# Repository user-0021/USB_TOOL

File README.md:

# BLDC_MOTER_DRIVER_ALPHA
この回路は15~30Vほどの電源で回す三層モータードライバー向けの回路です
設計上の連続最大電流は10Aです(実験してないのでだめかも)
ヒートシンクとかで冷やしながらならFET的には35A行ける
## インターフェース
制御用のインターフェースはLVDSとなっております。
## 機能
ゲートドライバーに過電圧過電流などの保護があります  
ホールセンサの入力はアナログ入力になっているのでプログラムを書けばどのセンサタイプでも  
いけるはず

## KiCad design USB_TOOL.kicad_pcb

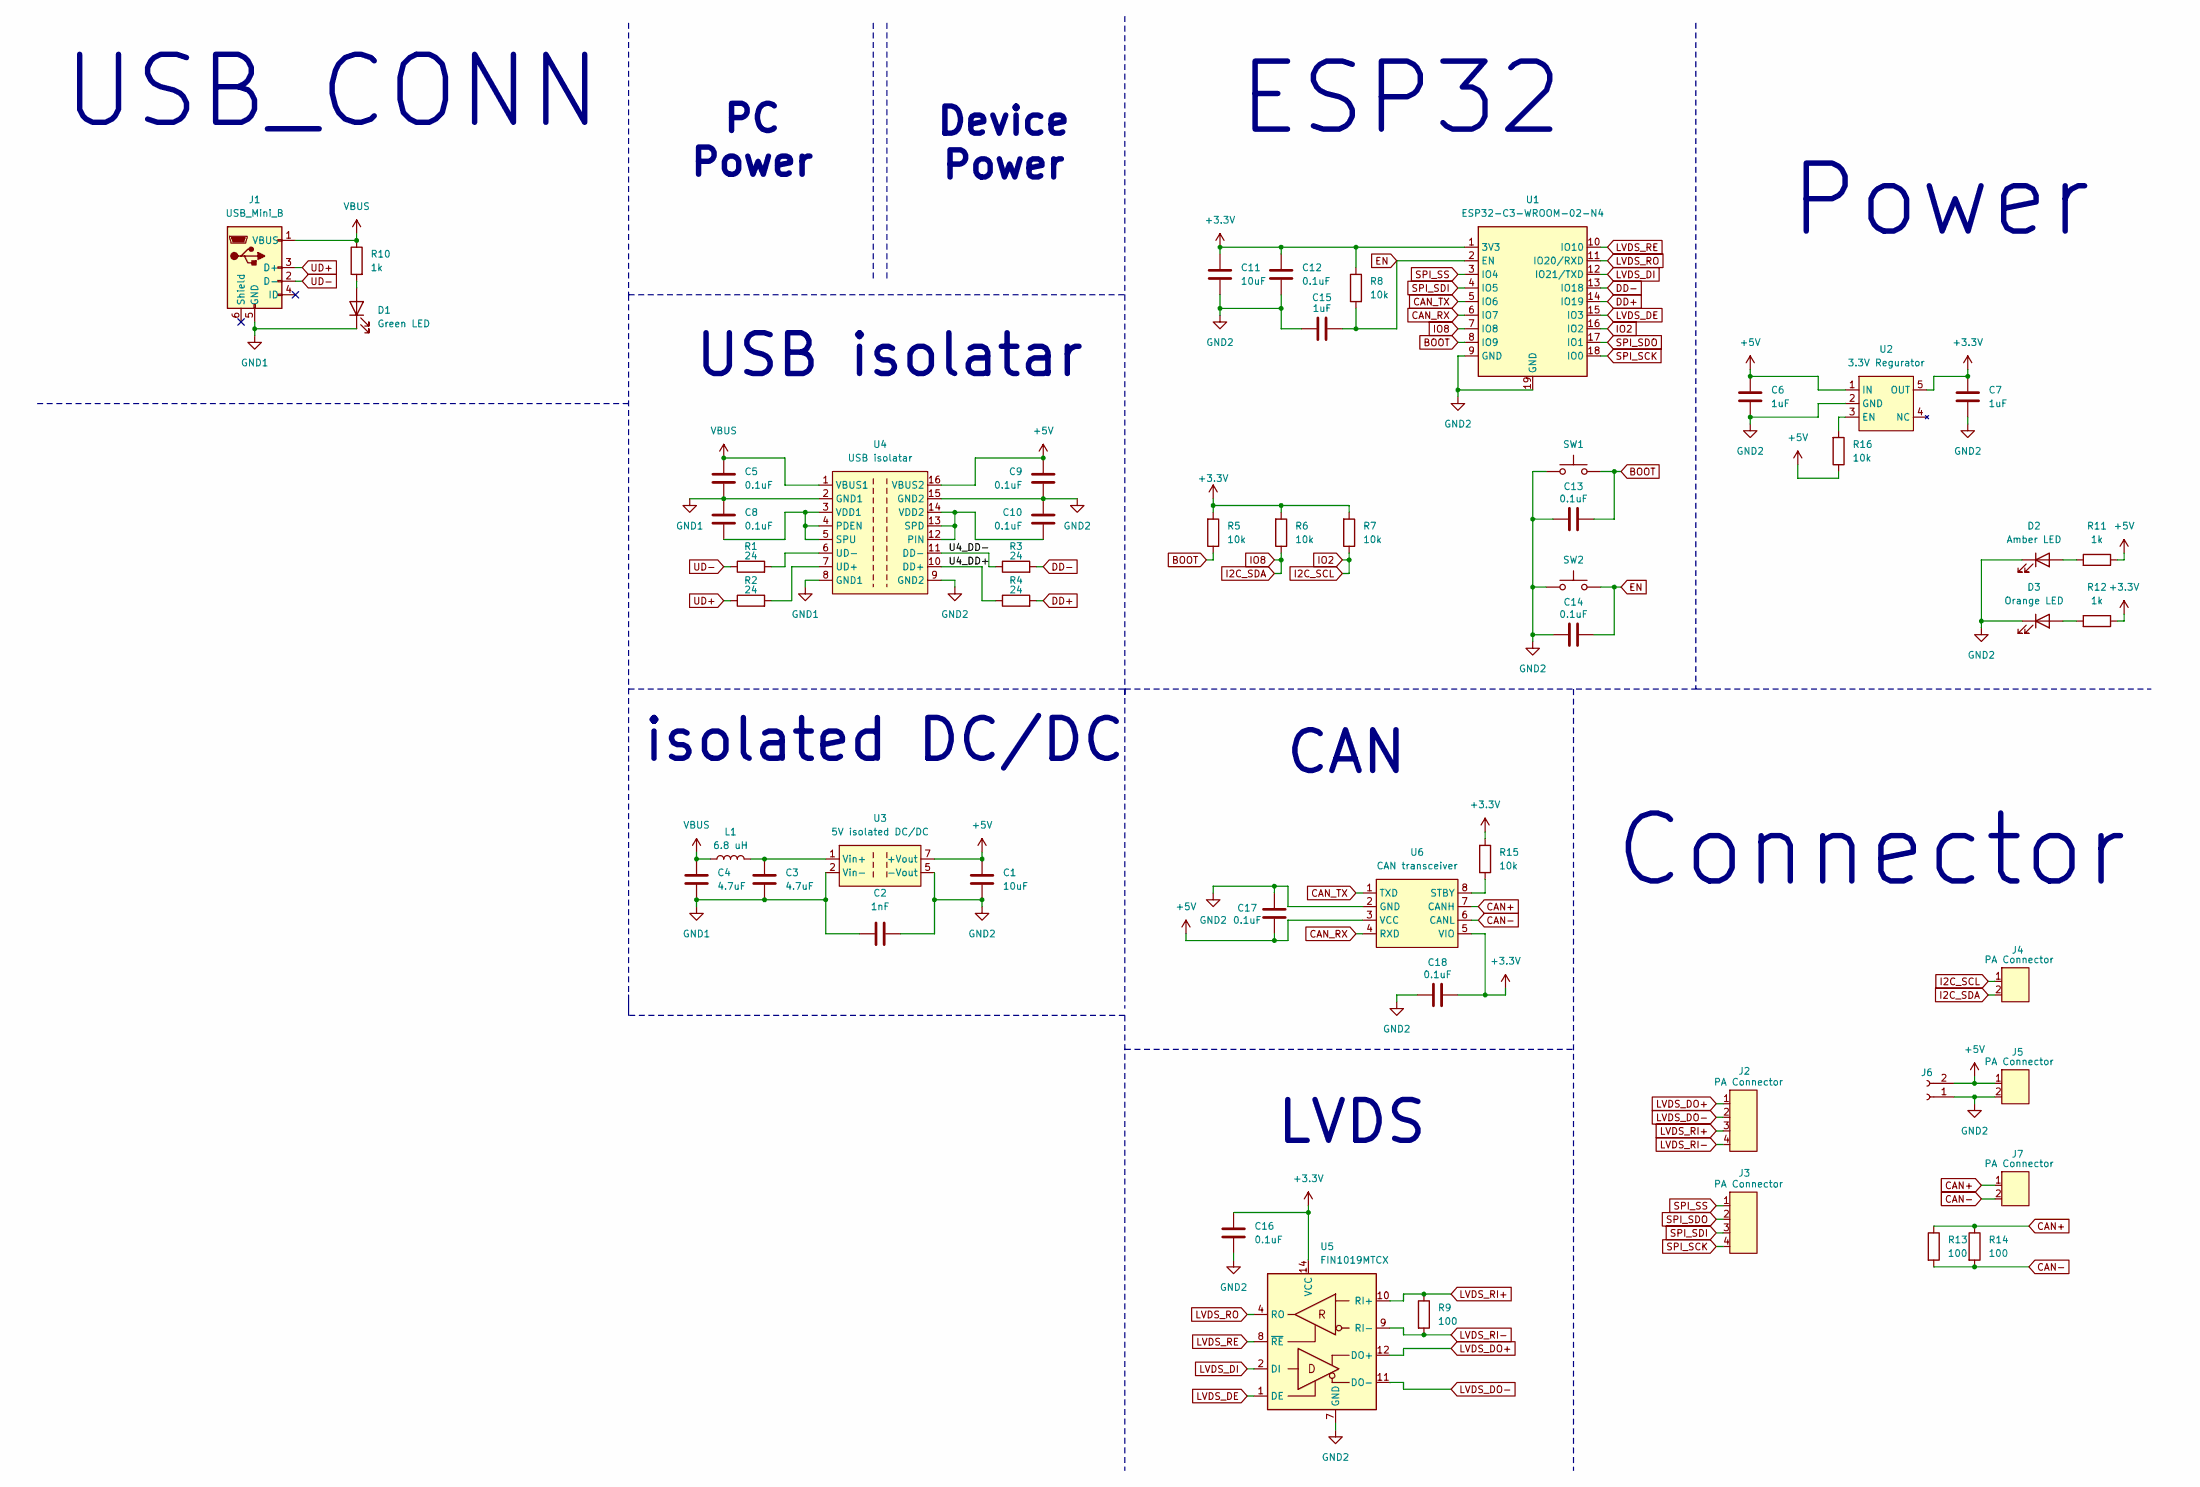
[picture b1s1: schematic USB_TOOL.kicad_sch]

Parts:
C1, C11: 10uF; C_1206_3216Metric; digikey 1276-1804-1-ND
C2: 1nF; C_1808_4520Metric; digikey 4587-C1808X102K402TCT-ND
C3, C4: 4.7uF; C_0603_1608Metric; digikey 490-7203-1-ND
C5, C8, C9, C10, C12, C13, C14, C16, C17, C18: 0.1uF; C_0603_1608Metric; digikey none
C6, C7, C15: 1uF; C_0805_2012Metric; digikey 1276-1029-1-ND
D1: Green LED; LED_0603_1608Metric; digikey 3147-B1911PG--20D000514U1930CT-ND
D2: Amber LED; LED_0603_1608Metric; digikey 3147-B1931UY--20D000114U1930CT-ND
D3: Orange LED; LED_0603_1608Metric; digikey 3147-B1911UD--20D001014U1930CT-ND
J1: USB_Mini_B; MUSB-5BF01AS; digikey none
J2, J3: PA Connector; S04B-PASK-2; digikey 455-S04B-PASK-2-ND
J4, J5, J7: PA Connector; S02B-PASK-2; digikey 455-S02B-PASK-2-ND
J6: Conn_01x02_Socket; PinHeader_1x02_P2.54mm_Vertical
L1: 6.8 uH; L_1210_3225Metric; digikey 3526-WIP322512A-6R8MLDGCT-ND
R1, R2, R3, R4: 24; R_0402_1005Metric; digikey YAG3073CT-ND
R5, R6, R7, R8, R15, R16: 10k; R_0603_1608Metric; digikey 4988-NRC06F1002TRFCT-ND
R9, R13, R14: 100; R_0402_1005Metric; digikey 2019-RK73H1ETTP1000FCT-ND
R10, R11, R12: 1k; R_0603_1608Metric; digikey 4988-NRC06F1001TRFCT-ND
SW1, SW2: SW_PUSH_1P1T_6x3.5mm_H4.3_APEM_MJTP1243; digikey CKN12304-ND
U1: ESP32-C3-WROOM-02-N4; digikey none
U2: 3.3V Regurator; SOT-23-5; digikey 31-AP7366EA-33W5-7CT-ND
U3: 5V isolated DC/DC; AM3DS-0505SH30LPZ; digikey 5245-AM3DS-0505SH30LPZ-ND
U4: USB isolatar; SOIC-16W_7.5x10.3mm_P1.27mm; digikey ADUM3160BRWZ-RLCT-ND
U5: FIN1019MTCX; TSSOP-14_4.4x5mm_P0.65mm; digikey FIN1019MTCXCT-ND
U6: CAN transceiver; SOIC-8_3.9x4.9mm_P1.27mm; digikey ATA6561-GAQW-NCT-ND

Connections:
+3.3V: C7.1, C11.1, C12.1, C16.1, C18.2, R5.1, R6.1, R7.1, R8.2, R12.2, R15.1, U1.1 (3V3), U2.5 (OUT), U5.14 (VCC), U6.5 (VIO)
+5V: C1.1, C6.1, C9.1, C17.1, J5.1, J6.2, R11.2, R16.2, U2.1 (IN), U3.7 (+Vout), U4.16 (VBUS2), U6.3 (VCC)
/U4_DD+: R4.1, U4.10 (DD+)
/U4_DD-: R3.1, U4.11 (DD-)
BOOT: C13.2, R5.2, SW1.2, U1.8 (IO9)
CAN+: J7.1, R13.1, R14.1, U6.7 (CANH)
CAN-: J7.2, R13.2, R14.2, U6.6 (CANL)
CAN_RX: U1.6 (IO7), U6.4 (RXD)
CAN_TX: U1.5 (IO6), U6.1 (TXD)
DD+: R4.2, U1.14 (IO19)
DD-: R3.2, U1.13 (IO18)
EN: C14.2, C15.2, R8.1, SW2.2, U1.2 (EN)
GND1: C2.1, C3.2, C4.2, C5.2, C8.1, D1.1 (K), J1.5 (GND), U3.2 (Vin-), U4.2 (GND1), U4.8 (GND1)
GND2: C1.2, C2.2, C6.2, C7.2, C9.2, C10.1, C11.2, C12.2, C13.1, C14.1, C15.1, C16.2, C17.2, C18.1, D2.1 (K), D3.1 (K), J5.2, J6.1, SW1.1, SW2.1, U1.9 (GND), U1.19 (GND), U2.2 (GND), U3.5 (-Vout), U4.9 (GND2), U4.15 (GND2), U5.7 (GND), U6.2 (GND)
I2C_SCL: J4.1, R7.2, U1.16 (IO2)
I2C_SDA: J4.2, R6.2, U1.7 (IO8)
LVDS_DE: U1.15 (IO3), U5.1 (DE)
LVDS_DI: U1.12 (IO21/TXD), U5.2 (DI)
LVDS_DO+: J2.1, U5.12 (DO+)
LVDS_DO-: J2.2, U5.11 (DO-)
LVDS_RE: U1.10 (IO10), U5.8 (~RE)
LVDS_RI+: J2.3, R9.1, U5.10 (RI+)
LVDS_RI-: J2.4, R9.2, U5.9 (RI-)
LVDS_RO: U1.11 (IO20/RXD), U5.4 (RO)
unnamed: D1.2 (A), R10.1
unnamed: D2.2 (A), R11.1
unnamed: D3.2 (A), R12.1
unnamed: R16.1, U2.3 (EN)
unnamed: C3.1, L1.2, U3.1 (Vin+)
unnamed: C8.2, U4.3 (VDD1), U4.4 (PDEN), U4.5 (SPU)
unnamed: C10.2, U4.12 (PIN), U4.13 (SPD), U4.14 (VDD2)
unnamed: R2.2, U4.7 (UD+)
unnamed: R1.2, U4.6 (UD-)
unnamed: R15.2, U6.8 (STBY)
SPI_SCK: J3.4, U1.18 (IO0)
SPI_SDI: J3.3, U1.4 (IO5)
SPI_SDO: J3.2, U1.17 (IO1)
SPI_SS: J3.1, U1.3 (IO4)
UD+: J1.3 (D+), R2.1
UD-: J1.2 (D-), R1.1
VBUS: C4.1, C5.1, J1.1 (VBUS), L1.1, R10.2, U4.1 (VBUS1)

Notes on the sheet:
Connector
USB_CONN
CAN
PC Power
isolated DC/DC
Device Power
LVDS
USB isolatar
ESP32
Power

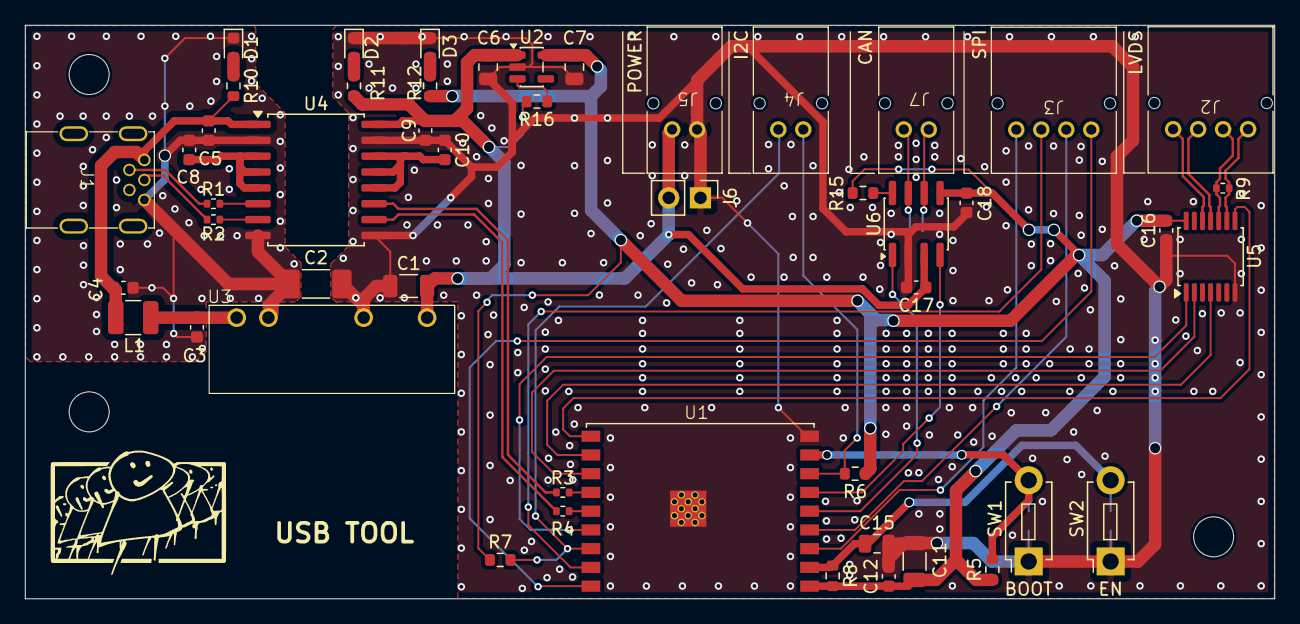
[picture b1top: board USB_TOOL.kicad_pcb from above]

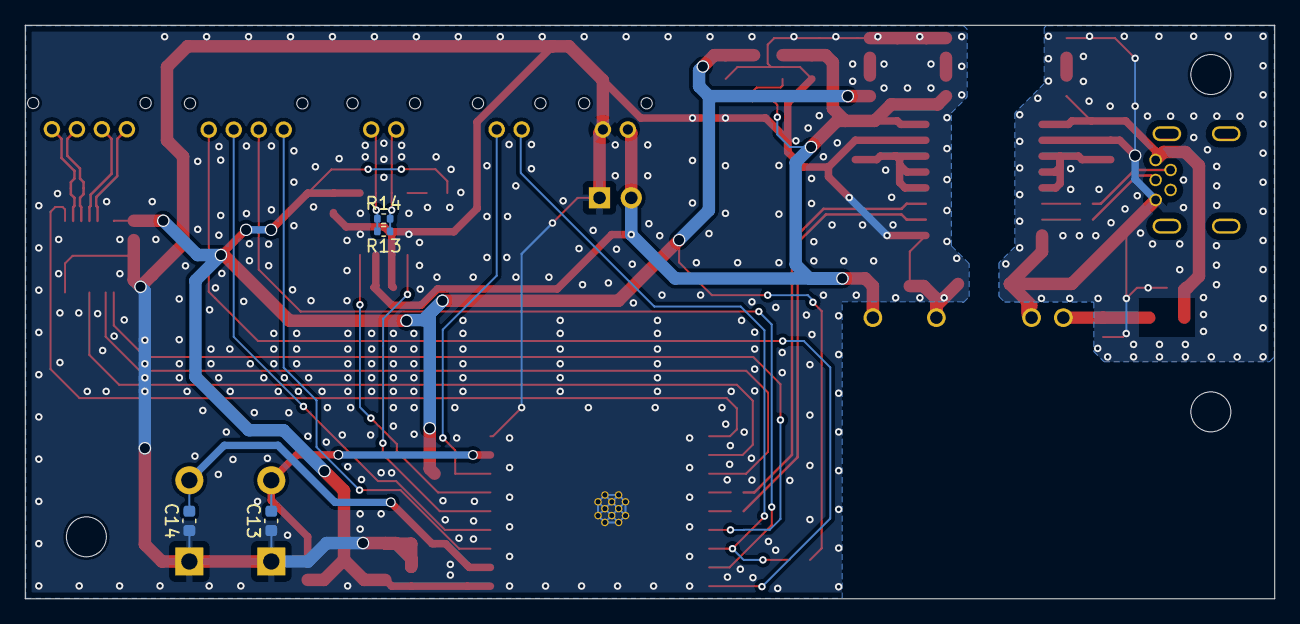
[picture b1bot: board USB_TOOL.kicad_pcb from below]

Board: 2 copper layers, 100.0 x 45.9 mm, 53 parts (4 on the bottom side), 41 nets.

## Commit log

2025-11-19 pull
2025-11-20 56789
